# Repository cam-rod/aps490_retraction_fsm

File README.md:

# Capstone FSM proototype

This is a logic prototype of an FSM being used in my capstone project. The code
doesn't actually run — the main focus was on verifying the design of the FSM,
and practicing some Rust along the way (especially the
[proc-macro](retract_fsm_transition/src/lib.rs) I put together).

## License

If you really want it, the code is licensed under [GPL-2.0-only](LICENSE).

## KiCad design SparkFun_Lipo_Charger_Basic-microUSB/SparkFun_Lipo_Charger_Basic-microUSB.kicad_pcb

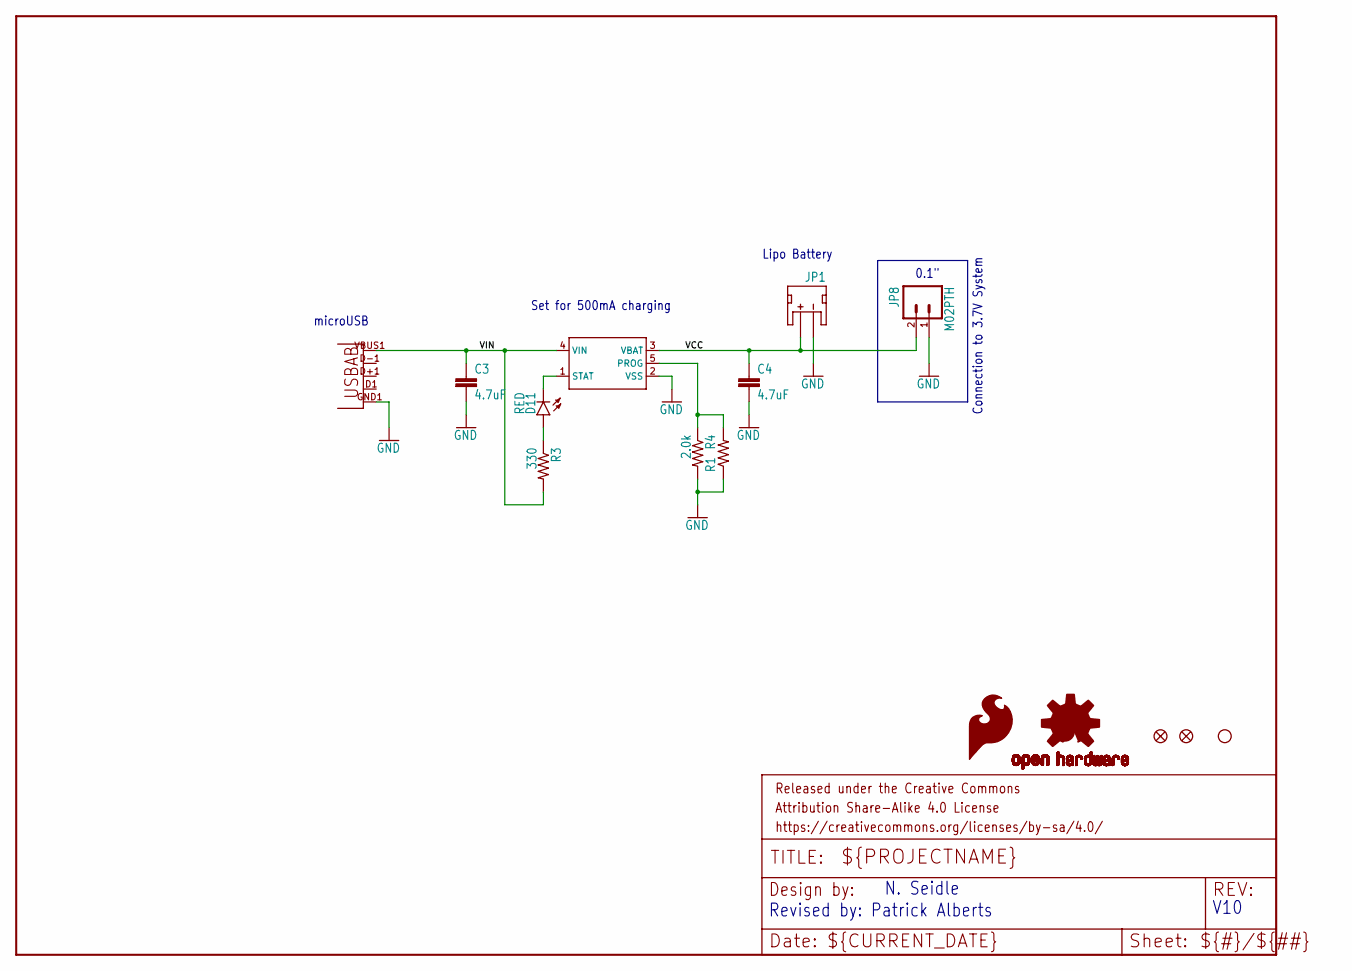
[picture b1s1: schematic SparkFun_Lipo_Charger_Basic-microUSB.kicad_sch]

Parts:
C3, C4: 4.7uF; 0603-CAP
D11: RED; LED-0603
FRAME1: FRAME-LETTER; CREATIVE_COMMONS
JP1: JST; JST-2-SMD
JP2: STAND-OFF
JP3, JP4: FIDUCIAL1X2; FIDUCIAL-1X2
JP8: M02PTH; 1X02
JP9: Micro USB; USB-AB-MICRO-SMD_V03
LOGO1: OSHW-LOGOS; OSHW-LOGO-S
LOGO2: SFE_LOGO_FLAME.1_INCH; SFE_LOGO_FLAME_.1
R1: RESISTORPTH-1/4W-VERT-KIT; AXIAL-0.1EZ
R3: 330; 0603-RES
R4: 2.0k; 0603-RES
U1: MCP73831; SOT23-5

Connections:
GND: C3.2, C4.2, JP1.1 (-), JP8.1, JP9.GND1 (GND), R1.P$1 (1), R4.2, U1.2 (VSS)
unnamed: D11.A, R3.1
PROG: R1.P$2 (2), R4.1, U1.5 (PROG)
STAT: D11.C, U1.1 (STAT)
VCC: C4.1, JP1.2 (+), JP8.2, U1.3 (VBAT)
VIN: C3.1, JP9.VBUS1 (VBUS), R3.2, U1.4 (VIN)

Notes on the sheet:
Connection to 3.7V System
Revised by: Patrick Alberts
N. Seidle
0.1"
Set for 500mA charging
Lipo Battery
V10
microUSB

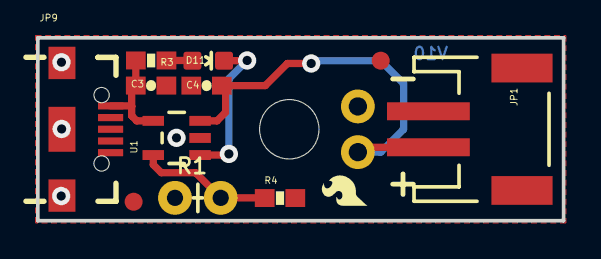
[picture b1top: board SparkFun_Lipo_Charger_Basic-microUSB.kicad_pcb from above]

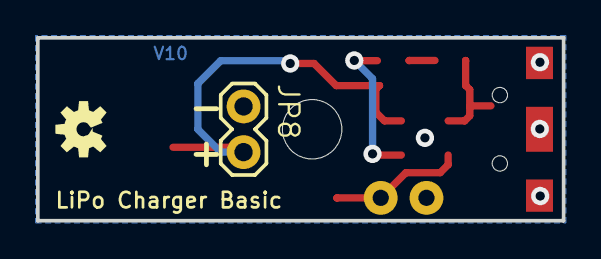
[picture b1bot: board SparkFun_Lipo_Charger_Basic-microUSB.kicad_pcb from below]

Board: 2 copper layers, 29.2 x 10.2 mm, 16 parts (2 on the bottom side), 6 nets.

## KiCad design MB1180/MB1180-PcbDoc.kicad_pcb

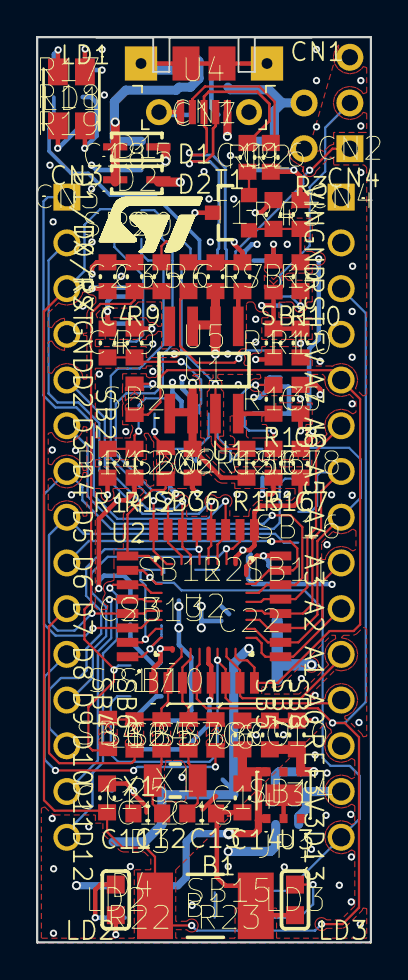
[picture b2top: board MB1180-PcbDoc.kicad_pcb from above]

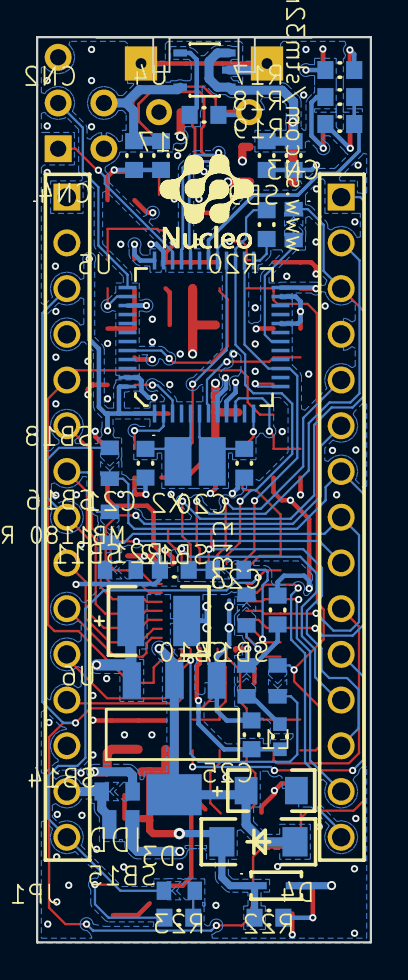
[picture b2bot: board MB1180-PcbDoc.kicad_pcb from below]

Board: 4 copper layers, 18.5 x 50.3 mm, 89 parts (38 on the bottom side), 79 nets.

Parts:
B1: B1; SW2_5R6_5R5x3R1
C1: C1; 0603C
C2: C2; 0603C
C3: C3; 0603C
C4: C4; 0603C
C5: C5; 0603C
C6: C6; 0603C
C7: C7; 0603C
C8: C8; 0603C
C9: C9; 0603C
C10: C10; 0603C
C11: C11; 0603C
C12: C12; 0603C
C13: C13; 0603C
C14: C14; 0603C
C15: C15; 0603C
C16: C16; 0603C
C17: C17; 0603C
C18: C18; 0603C
C19: C19; 0603C
C20: C20; 0603C
C21: C21; 0603C
C22: C22; TAN_B
C23: C23; 0603C
C24: C24; 0603C
C25: C25; TAN_A
CN1: CN1; Molex_1050170001
CN2: CN2; HDR_1x5_2R54_V_M
CN3: CN3; HDR_1x15_2R54_V_F
CN4: CN4; HDR_1x15_2R54_V_F
D1: D1; SOD-323
D2: D2; SOD-323
D3: D3; SMA
D4: D4; SOD-323
JP1: JP1; HDR_1x2_1R27_R_M
L1: L1; 0603L
LD1: LD1; HSMF-A201
LD2: LD2; 0603D_R
LD3: LD3; 0603D_G
R1: R1; 0603R
R2: R2; 0603R
R3: R3; 0603R
R4: R4; 0603R
R5: R5; 0603R
R6: R6; 0603R
R7: R7; 0603R
R8: R8; 0603R
R9: R9; 0603R
R10: R10; 0603R
R11: R11; 0603R
R12: R12; 0603R
R13: R13; 0603R
R14: R14; 0603R
R15: R15; 0603R
R16: R16; 0603R
R17: R17; 0603R
R18: R18; 0603R
R19: R19; 0603R
R20: R20; 0603R
R21: R21; 0603R
R22: R22; 0603R
R23: R23; 0603R
SB1: SB1; SB_0603
SB2: SB2; SB_0603
SB3: SB3; SB_0603
SB4: SB4; SB_0603
SB5: SB5; SB_0603
SB6: SB6; SB_0603
SB7: SB7; SB_0603
SB8: SB8; SB_0603
SB9: SB9; SB_0603
SB10: SB10; SB_0603
SB11: SB11; SB_0603
SB12: SB12; SB_0603
SB13: SB13; SB_0603
SB14: SB14; SB_0603
SB15: SB15; SB_0603
SB16: SB16; SB_0603
SB17: SB17; SB_0603
SB18: SB18; SB_0603
T1: T1; SOT23-3
U1: U1; SO-8
U2: U2; LQFP32_0R5_7x7
U3: U3; DFN6_0R95_3x3_TP
U4: U4; SOT23-5L
U5: U5; LQFP48_0R5_7x7
U6: U6; SOT-223
X1: X1; XTAL_2SM_3R2X1R5
X2: X2; XTAL_2SM_3R2x2R5

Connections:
+3V3: CN4.14, JP1.1, SB14.2
+3V3_ST_LINK: C2.2, C5.2, C16.1, C19.2, CN2.4, R9.2, R17.2, SB1.1, T1.3, U4.5, U5.1, U5.9, U5.24, U5.36, U5.48
+5V: C8.2, C14.1, CN4.4, D3.2, D4.2, R22.2, U3.1, U3.6
AIN_1: R12.2, R14.2, U5.10
AVDD: C24.1, CN4.13, L1.1, U2.5
BOOT0: R21.1, SB12.2
E5V: C25.1, D2.1, D3.1, R11.1, U6.2, U6.4
GND: B1.2, C1.1, C2.1, C3.2, C4.1, C5.1, C6.1, C7.2, C8.1, C9.2, C10.1, C11.1, C12.2, C13.2, C14.2, C15.1, C16.2, C17.1, C18.1, C19.1, C20.2, C21.2, C22.2, C23.2, C24.2, C25.2, CN1.5, CN1.6, CN1.7, CN1.8, CN1.9, CN1.10, CN1.11, CN2.2, CN3.4, CN4.2, LD1.1, LD2.2, LD3.2, R2.2, R3.1, R6.1, R7.2, R10.2, R12.1, R13.1, R16.1, R21.2, SB11.2, SB13.2, U1.4, U3.0, U3.2, U4.2, U5.8, U5.20, U5.23, U5.35, U5.47, U6.1
LED_STLINK: R18.1, R19.1, U5.30
MCO: C3.1, R5.2, SB4.1, SB17.1
NRST: B1.1, C11.2, CN3.3, CN4.3, SB9.2, U2.4
NetC12_1: C12.1, SB5.1, X1.1
NetC13_1: C13.1, SB7.1, X1.2
NetC15_2: C15.2, C18.2, D1.2, D2.2, U4.1, U4.3
NetC17_2: C17.2, U4.4
NetCN1_4: CN1.4, R2.1
NetL1_2: L1.2, SB10.1
NetLD1_2: LD1.2, R18.2
NetLD1_3: LD1.3, R19.2
NetLD1_4: LD1.4, R17.1
NetLD2_1: LD2.1, R22.1
NetLD3_1: LD3.1, R23.1
NetR1_2: R1.2, T1.1
NetR3_2: R3.2, R4.1, R8.1, T1.2
NetR5_1: R5.1, U5.29
NetR6_2: R6.2, U5.44
NetR7_1: R7.1, U1.5
NetR10_1: R10.1, R11.2, SB1.2, U5.39
NetR13_2: R13.2, U5.3
NetR16_2: R16.2, U5.2
NetR23_2: R23.2, SB15.1
NetSB4_2: SB4.2, SB5.2, SB6.2, U2.2
NetSB7_2: SB7.2, SB8.2, U2.3
NetSB11_1: SB11.1, U2.16
NetSB12_1: SB12.1, U2.31
NetSB13_1: SB13.1, U2.32
OSC_IN: C21.1, U5.5, X2.2
OSC_OUT: C20.1, U5.6, X2.1
PA0: CN4.12, SB17.2, U2.6
PA1: CN4.11, U2.7
PA2: CN4.5, SB2.1, U2.8
PA3: CN4.10, U2.9
PA4: CN4.9, U2.10
PA5: CN4.8, SB18.1, U2.11
PA6: CN4.7, SB16.1, U2.12
PA7: CN4.6, U2.13
PA8: CN3.12, U2.18
PA9: CN3.1, U2.19
PA10: CN3.2, U2.20
PA11: CN3.13, U2.21
PA12: CN3.5, U2.22
PA13: R20.2, U2.23, U5.27
PA14: U2.24, U5.15, U5.26
PA15: SB3.1, U2.25
PB0: CN3.6, U2.14
PB1: CN3.9, U2.15
PB3: CN4.15, SB15.2, U2.26
PB4: CN3.15, U2.27
PB5: CN3.14, U2.28
PB6: CN3.8, SB16.2, U2.29
PB7: CN3.7, SB18.2, U2.30
PF0: CN3.10, SB6.1
PF1: CN3.11, SB8.1
PWR_ENN: R15.2, U1.3, U5.28
STLINK_RX: SB2.2, U5.13
STLINK_TX: SB3.2, U5.12
STM_JTCK: CN2.3, U5.37
STM_JTMS: CN2.1, U5.34
STM_RST: C4.2, R9.1, U5.7
T_NRST: SB9.1, U5.18
T_SWDIO_IN: R20.1, U5.25
U5V: C6.2, CN1.1, D1.1, R4.2, R15.1, U1.1, U1.2
U5V_ST_LINK: C1.2, D4.1, U1.6, U1.7
USB_DM: CN1.2, U5.32
USB_DP: CN1.3, R1.1, U5.33
USB_RENUMN: R8.2, U5.38
VDD: C7.1, C23.1, JP1.2, SB10.2, U2.1, U2.17
VIN: C22.1, CN4.1, U6.3
VO: C9.1, C10.2, R14.1, SB14.1, U3.4

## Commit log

2024-01-06 initial FSM version
2024-01-08 MACROS, and sensor representations
2024-01-08 most states complete except error handling
2024-01-08 the completed rough FSM
2024-01-09 now with LEDs
2024-01-09 small watchdog note
2024-01-09 README and licensing
2024-01-11 detection research
2024-01-22 nucleo32 schematic, detection hardware start
2024-01-22 Link Nucleo32 into main HW project
2024-01-25 add some components
2024-03-12 move all old files to concept crate
2024-03-18 understanding embedded_hal
2024-03-20 add states, modify initialization code
2024-03-20 still major arch decisions
2024-03-20 fixed component initialization
2024-03-20 add signal gen
2024-03-21 starting ADC
2024-03-21 add buffer for samples
2024-03-21 working on disable switch
2024-03-21 add placeholder impl of disable switch
2024-03-21 documentation of public fields
2024-03-24 add KiCAD for LiPo board
2024-03-24 add lipo charger
2024-03-24 update schematic
2024-04-02 add zipped code for report submission
2024-04-02 restructure in progress

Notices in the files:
SparkFun_Lipo_Charger_Basic-microUSB/SparkFun_Lipo_Charger_Basic-microUSB.kicad_sch:
https://creativecommons.org/licenses/by-sa/4.0
Released under the Creative Commons
parts and their libraries:
Released under the Creative Commons Attribution Share-Alike 4.0 License
